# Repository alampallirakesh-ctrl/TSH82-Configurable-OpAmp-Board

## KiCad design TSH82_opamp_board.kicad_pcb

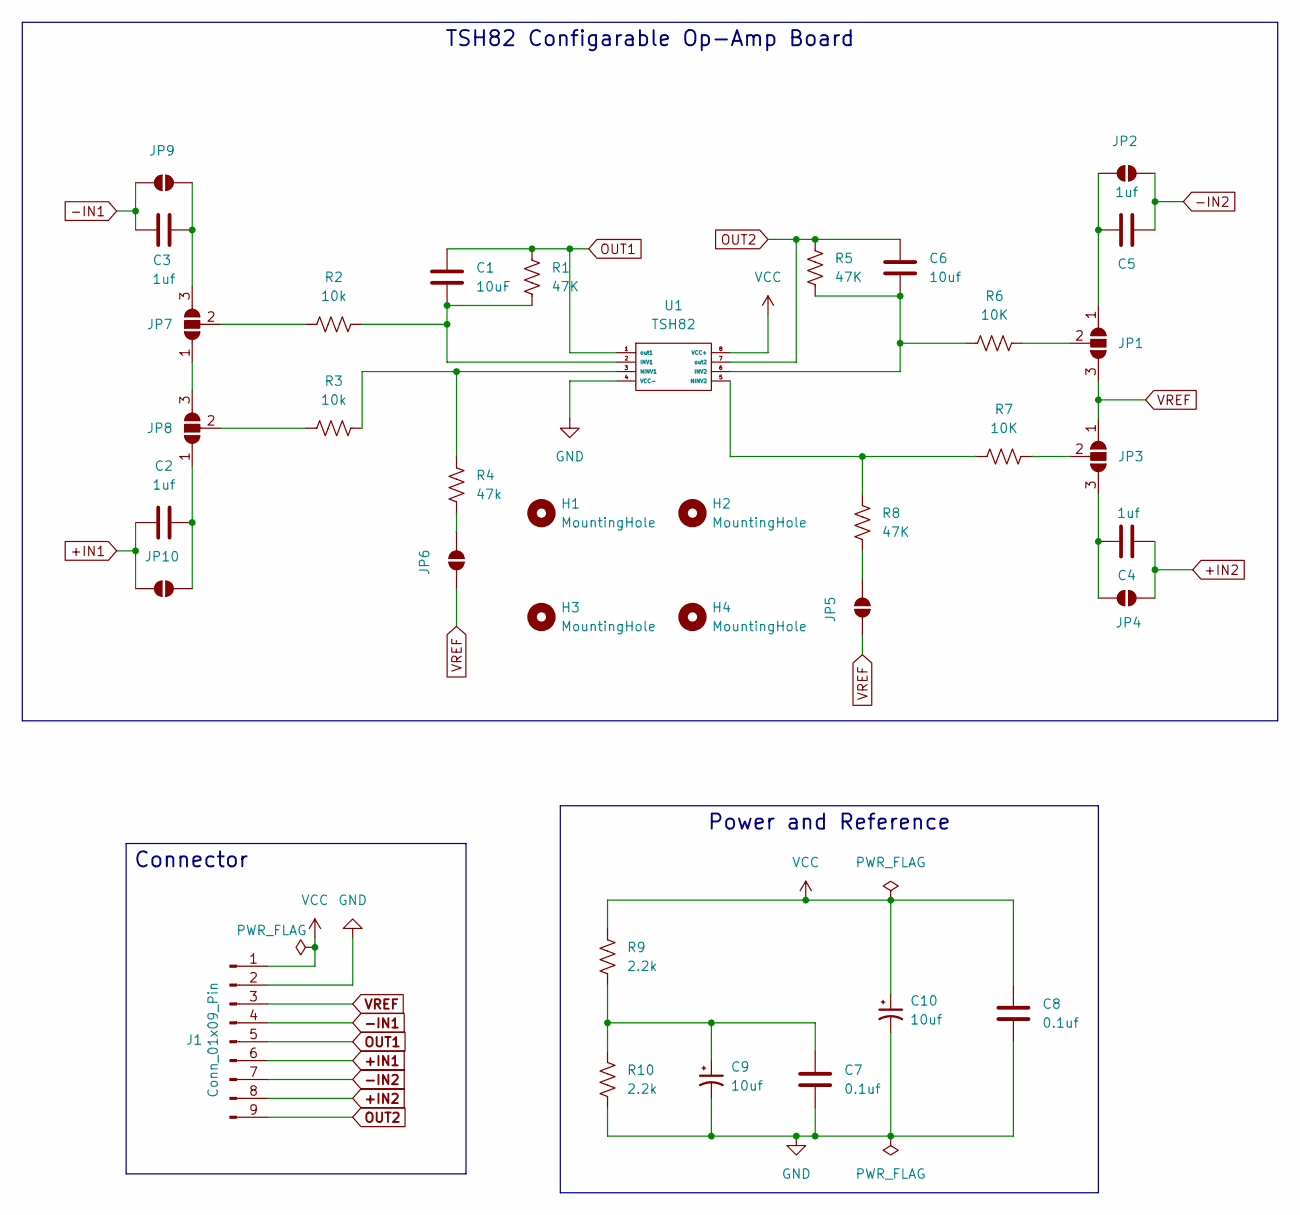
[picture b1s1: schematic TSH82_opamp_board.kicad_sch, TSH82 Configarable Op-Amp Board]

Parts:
C1: 10uF; C_0805_2012Metric_Pad1.18x1.45mm_HandSolder
C2, C3, C4, C5: 1uf; C_1206_3216Metric_Pad1.33x1.80mm_HandSolder
C6: 10uf; C_0805_2012Metric_Pad1.18x1.45mm_HandSolder
C7, C8: 0.1uf; C_1206_3216Metric_Pad1.33x1.80mm_HandSolder
C9, C10: 10uf; CP_Elec_4x3
H1, H2, H3, H4: MountingHole; MountingHole_2.1mm
J1: Conn_01x09_Pin; PinHeader_1x09_P2.54mm_Vertical
JP1, JP3, JP7, JP8: SolderJumper_3_Open; SolderJumper-3_P1.3mm_Open_RoundedPad1.0x1.5mm
JP2, JP4, JP5, JP6, JP9, JP10: SolderJumper_2_Open; SolderJumper-2_P1.3mm_Open_RoundedPad1.0x1.5mm
R1, R5, R8: 47K; R_0805_2012Metric_Pad1.20x1.40mm_HandSolder
R2, R3: 10k; R_0805_2012Metric_Pad1.20x1.40mm_HandSolder
R4: 47k; R_0805_2012Metric_Pad1.20x1.40mm_HandSolder
R6, R7: 10K; R_0805_2012Metric_Pad1.20x1.40mm_HandSolder
R9, R10: 2.2k; R_0805_2012Metric_Pad1.20x1.40mm_HandSolder
U1: TSH82; SOIC-8

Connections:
+IN1: C2.1, J1.6, JP10.1 (A)
+IN2: C4.1, J1.8, JP4.2 (B)
-IN1: C3.1, J1.4, JP9.1 (A)
-IN2: C5.1, J1.7, JP2.2 (B)
GND: C7.2, C8.2, C9.2, C10.2, J1.2, R10.2, U1.4 (VCC-)
unnamed: C7.1, C9.1, R9.2, R10.1
unnamed: C5.2, JP1.1 (A), JP2.1 (A)
unnamed: JP1.2 (C), R6.2
unnamed: C4.2, JP3.3 (B), JP4.1 (A)
unnamed: JP3.2 (C), R7.2
unnamed: JP5.2 (B), R8.2
unnamed: JP6.2 (B), R4.2
unnamed: JP7.1 (A), JP8.3 (B)
unnamed: C3.2, JP7.3 (B), JP9.2 (B)
unnamed: JP7.2 (C), R2.1
unnamed: JP8.2 (C), R3.1
unnamed: C2.2, JP8.1 (A), JP10.2 (B)
unnamed: C1.2, R1.2, R2.2, U1.2 (INV1)
unnamed: C6.2, R5.2, R6.1, U1.6 (INV2)
unnamed: R3.2, R4.1, U1.3 (NINV1)
unnamed: R7.1, R8.1, U1.5 (NINV2)
OUT1: C1.1, J1.5, R1.1, U1.1 (out1)
OUT2: C6.1, J1.9, R5.1, U1.7 (out2)
VCC: C8.1, C10.1, J1.1, R9.1, U1.8 (VCC+)
VREF: J1.3, JP1.3 (B), JP3.1 (A), JP5.1 (A), JP6.1 (A)

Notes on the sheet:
TSH82 Configarable Op-Amp Board
Power and Reference
Connector

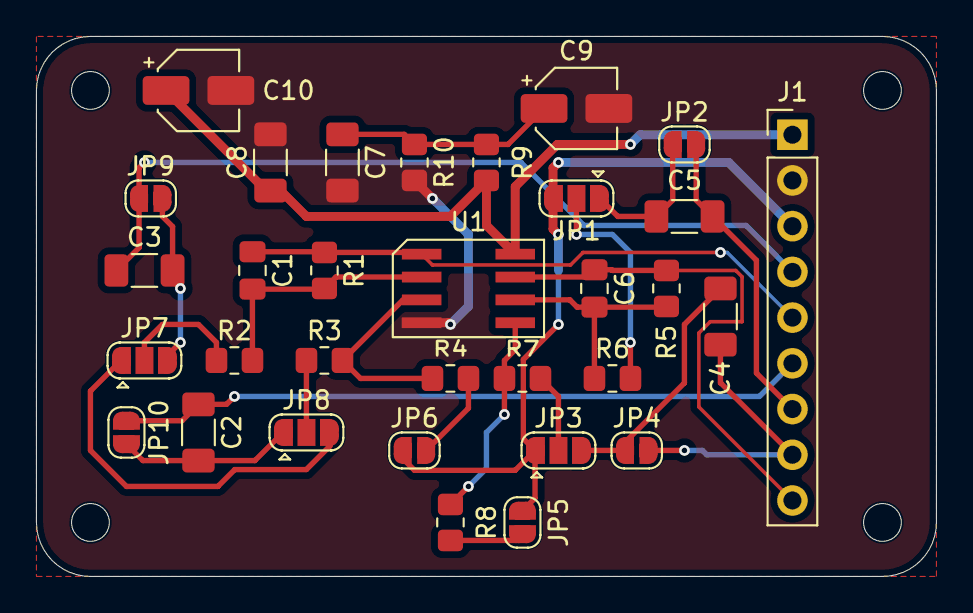
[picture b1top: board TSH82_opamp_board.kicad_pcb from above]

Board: 2 copper layers, 50.0 x 30.0 mm, 36 parts (0 on the bottom side), 25 nets.
